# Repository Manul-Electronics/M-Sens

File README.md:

# M-Sens
M-Sens is a family of Open Source and Open Hardware sensors.

For now on this family includes the following devices : 
- [ ] **(Work in progress)** Tropic : A headless relative humidity and temperature sensor build around the HTU31D from TE Connectivity 
- [ ] **(Work in progress)** Mother : A Raspberry Pi based gateway with support for a variaty of communication protocols (Ethernet, Wi-Fi, BLE, Zigbee, ...) built to act as home automation server and central point.

*Other devices could join the family in the future but as I work alone it could be in a very long time.*

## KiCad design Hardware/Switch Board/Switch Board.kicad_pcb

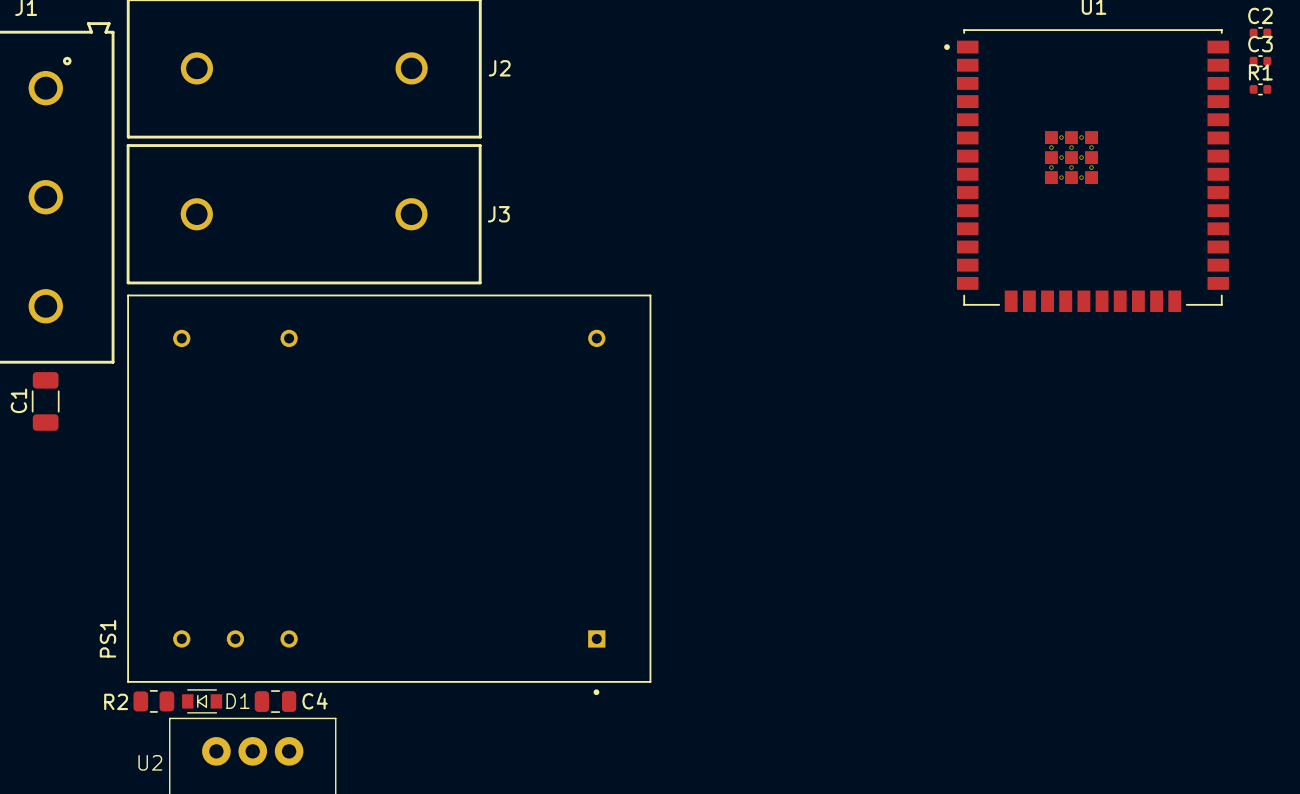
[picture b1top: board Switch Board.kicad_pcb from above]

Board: 2 copper layers, 13 parts (0 on the bottom side), 10 nets, no tracks yet.

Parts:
C1: TBD; C_1206_3216Metric
C2: 1uF; C_0402_1005Metric
C3: 100nF; C_0402_1005Metric
C4: 4.7uF; C_0805_2012Metric
D1: 150224RS73100A; LED_2214
J1: 691218410003
J2, J3: 696106003002
PS1: TMLM_04112; CONV_TMLM_04112
R1: 10K; C_0402_1005Metric
R2: 100R; R_0805_2012Metric
U1: ESP32-WROOM-32UE_(16MB); XCVR_ESP32-WROOM-32UE_(16MB)
U2: 173010335

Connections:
+3V3: C3.1, D1.2 (A), R1.1, U1.2 (3V3), U2.3 (VOUT)
+12V: C4.1, PS1.2 (+VOUT), U2.1 (VIN)
/PSU/L: J1.1, J2.1
/PSU/N: J1.2, J3.1
/mcu/EN: C2.1, R1.2, U1.3 (EN)
Earth_Protective: C1.2, J1.3
GND: C1.1, C2.2, C3.2, C4.2, PS1.3 (-VOUT), R2.2, U1.1 (GND), U1.15 (GND), U1.38 (GND), U1.39_1 (GND), U1.39_2 (GND), U1.39_3 (GND), U1.39_4 (GND), U1.39_5 (GND), U1.39_6 (GND), U1.39_7 (GND), U1.39_8 (GND), U1.39_9 (GND), U2.2 (GND)
unnamed: D1.1 (K), R2.1
unnamed: J2.2, PS1.5 (AC(L))
unnamed: J3.2, PS1.6 (AC(N))

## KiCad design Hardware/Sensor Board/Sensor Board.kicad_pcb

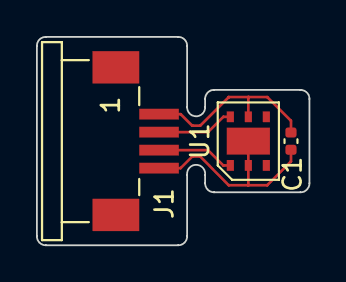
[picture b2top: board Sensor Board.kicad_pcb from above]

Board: 2 copper layers, 15.1 x 11.6 mm, 3 parts (0 on the bottom side), 4 nets.

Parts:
C1: 100nF; C_0402_1005Metric
J1: 68610414422
U1: HTU21DF

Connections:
+3V3: C1.1, J1.1, U1.5 (VDD)
GND: C1.2, J1.4, U1.2 (GND), U1.7 (PAD)
unnamed: J1.2, U1.6 (SCL)
unnamed: J1.3, U1.1 (SDA)

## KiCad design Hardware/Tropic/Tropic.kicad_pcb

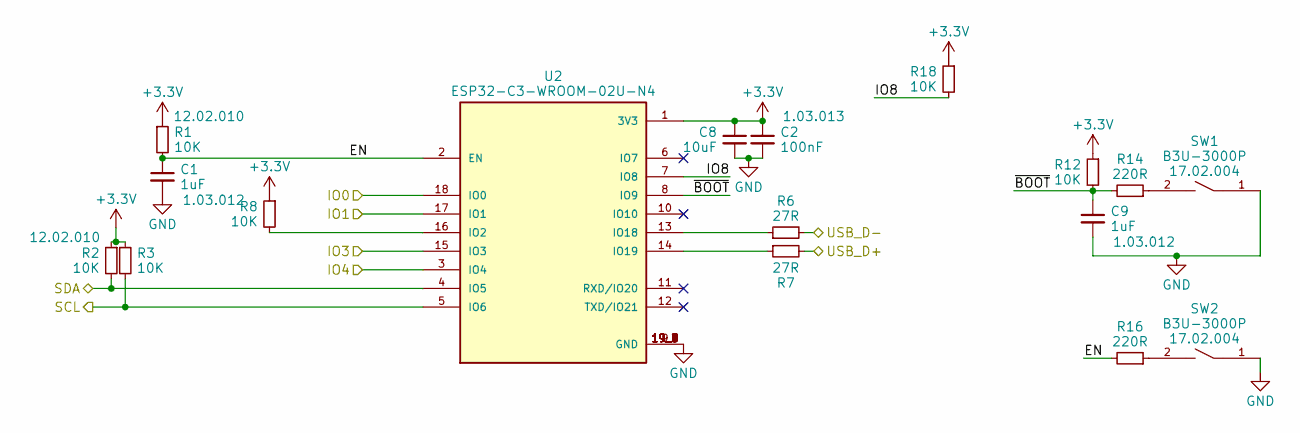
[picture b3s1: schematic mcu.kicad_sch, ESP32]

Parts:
C1, C9: 1uF; C_0402_1005Metric
C2: 100nF; C_0402_1005Metric
C8: 10uF; C_0402_1005Metric
R1, R2, R3, R8, R12, R18: 10K; R_0402_1005Metric
R6, R7: 27R; R_0402_1005Metric
R14, R16: 220R; R_0402_1005Metric
SW1, SW2: B3U-3000P; SW_B3U-3000P; mpn B3U-3000P
U2: ESP32-C3-WROOM-02U-N4; XCVR_ESP32-C3-WROOM-02U-N4

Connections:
+3.3V: C2.1, C8.1, R1.1, R2.1, R3.1, R8.1, R12.1, R18.1, U2.1 (3V3); also elsewhere on the board
/MCU/EN: C1.1, R1.2, R16.2, U2.2 (EN)
/MCU/IO0: U2.18 (IO0); also elsewhere on the board
/MCU/IO1: U2.17 (IO1); also elsewhere on the board
/MCU/IO3: U2.15 (IO3); also elsewhere on the board
/MCU/IO4: U2.3 (IO4); also elsewhere on the board
/MCU/IO8: R18.2, U2.7 (IO8)
/MCU/SCL: R3.2, U2.5 (IO6); also elsewhere on the board
/MCU/SDA: R2.2, U2.4 (IO5); also elsewhere on the board
/MCU/USB_D+: R7.2; also elsewhere on the board
/MCU/USB_D-: R6.2; also elsewhere on the board
/MCU/~BOOT: C9.1, R12.2, R14.2, U2.8 (IO9)
GND: C1.2, C2.2, C8.2, C9.2, SW1.1, SW2.1, U2.9 (GND), U2.19_1 (GND), U2.19_2 (GND), U2.19_3 (GND), U2.19_4 (GND), U2.19_5 (GND), U2.19_6 (GND), U2.19_7 (GND), U2.19_8 (GND), U2.19_9 (GND); also elsewhere on the board
unnamed: R14.1, SW1.2
unnamed: R16.1, SW2.2
unnamed: R8.2, U2.16 (IO2)
unnamed: R6.1, U2.13 (IO18)
unnamed: R7.1, U2.14 (IO19)

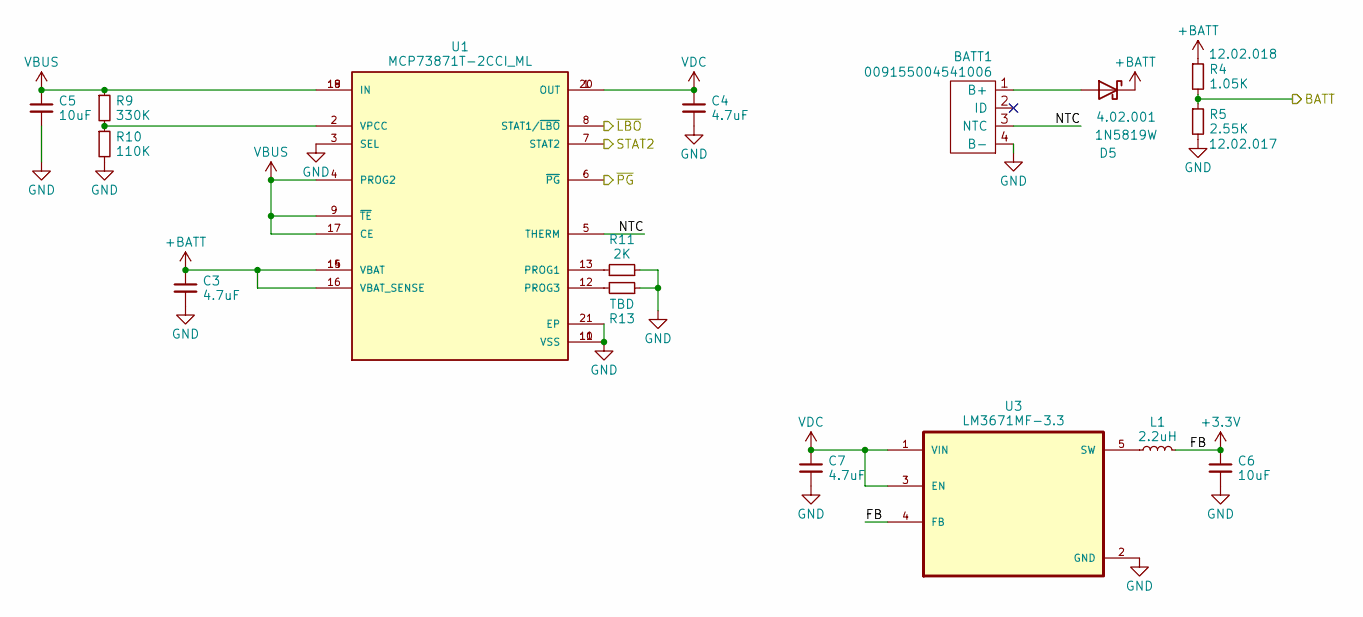
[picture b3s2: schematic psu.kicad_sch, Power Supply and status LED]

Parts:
BATT1: 009155004541006
C3, C4: 4.7uF; C_0603_1608Metric
C5: 10uF; C_0603_1608Metric
C6: 10uF; C_0603_1608Metric; MPN C1608X5R0J106K
C7: 4.7uF; C_0603_1608Metric; MPN C1608X5R0J475K
D5: 1N5819W; D_SOD-123; MPN 1N5819HW-7-F
L1: 2.2uH; CDRH2D14NP-2R2NC
R4: 1.05K; R_0402_1005Metric
R5: 2.55K; R_0402_1005Metric
R9: 330K; R_0402_1005Metric
R10: 110K; R_0402_1005Metric
R11: 2K; R_0402_1005Metric
R13: TBD; R_0402_1005Metric
U1: MCP73871T-2CCI_ML; QFN50P400X400X100-21N
U3: LM3671MF-3.3; SOT-23-5

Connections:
+3.3V: C6.1, L1.2, U3.4 (FB); also elsewhere on the board
+BATT: C3.1, D5.1 (K), R4.1, U1.14 (VBAT), U1.15 (VBAT), U1.16 (VBAT_SENSE)
/MCU/IO0: R4.2, R5.1; also elsewhere on the board
/MCU/IO1: U1.8 (STAT1/~LBO); also elsewhere on the board
/MCU/IO3: U1.6 (~PG); also elsewhere on the board
/MCU/IO4: U1.7 (STAT2); also elsewhere on the board
/Power Supply/NTC: BATT1.3 (NTC), U1.5 (THERM)
GND: BATT1.4 (B-), C3.2, C4.2, C5.2, C6.2, C7.2, R5.2, R10.2, R11.2, R13.2, U1.3 (SEL), U1.10 (VSS), U1.11 (VSS), U1.21 (EP), U3.2 (GND); also elsewhere on the board
unnamed: BATT1.1 (B+), D5.2 (A)
unnamed: R11.1, U1.13 (PROG1)
unnamed: R13.1, U1.12 (PROG3)
unnamed: R9.2, R10.1, U1.2 (VPCC)
unnamed: L1.1, U3.5 (SW)
VBUS: C5.1, R9.1, U1.4 (PROG2), U1.9 (~TE), U1.17 (CE), U1.18 (IN), U1.19 (IN); also elsewhere on the board
VDC: C4.1, C7.1, U1.1 (OUT), U1.20 (OUT), U3.1 (VIN), U3.3 (EN)

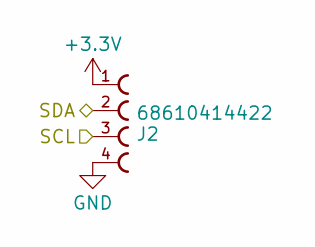
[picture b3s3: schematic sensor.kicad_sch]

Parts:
J2: 68610414422; MPN 68610414422

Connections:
+3.3V: J2.1; also elsewhere on the board
/MCU/SCL: J2.3; also elsewhere on the board
/MCU/SDA: J2.2; also elsewhere on the board
GND: J2.4; also elsewhere on the board

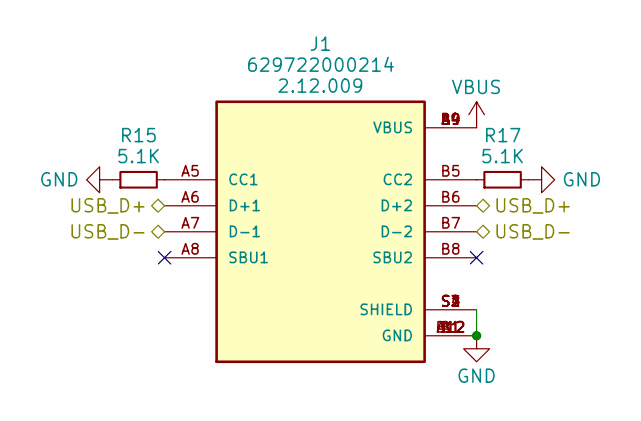
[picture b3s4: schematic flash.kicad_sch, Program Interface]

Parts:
J1: 629722000214; PARTREV 001.001
R15, R17: 5.1K; R_0402_1005Metric

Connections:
/MCU/USB_D+: J1.A6 (D+1), J1.B6 (D+2); also elsewhere on the board
/MCU/USB_D-: J1.A7 (D-1), J1.B7 (D-2); also elsewhere on the board
GND: J1.A1 (GND), J1.A12 (GND), J1.B1 (GND), J1.B12 (GND), J1.S1 (SHIELD), J1.S2 (SHIELD), J1.S3 (SHIELD), J1.S4 (SHIELD), R15.1, R17.2; also elsewhere on the board
unnamed: J1.A5 (CC1), R15.2
unnamed: J1.B5 (CC2), R17.1
VBUS: J1.A4 (VBUS), J1.A9 (VBUS), J1.B4 (VBUS), J1.B9 (VBUS); also elsewhere on the board

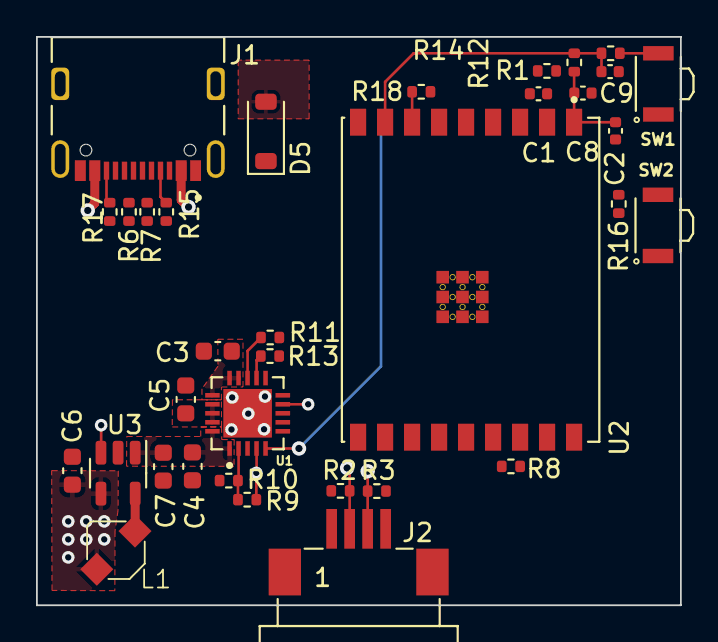
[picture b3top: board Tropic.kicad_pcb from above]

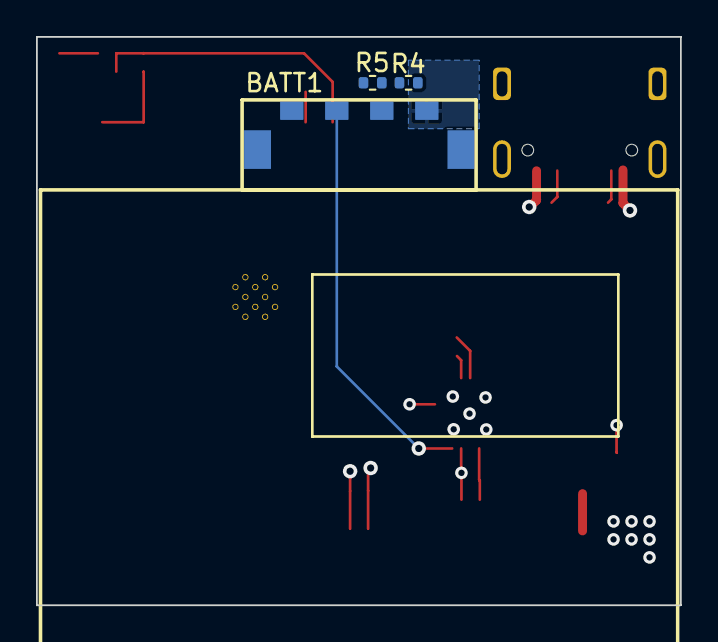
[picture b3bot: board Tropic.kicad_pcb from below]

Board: 4 copper layers, 35.8 x 31.6 mm, 37 parts (3 on the bottom side), 29 nets.

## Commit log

2024-01-31 Added Tropic and Tropic Thunder PCBs
2024-01-31 Removed doubled Pi Matching and add LED for voltage monitoring
2024-02-01 Completed design V1
2024-02-01 Add spacing around rf line
2024-02-02 Latest changes
2024-02-26 Rework on components
2024-12-13 Clear Hardware folder, reamking from scratch
2024-12-14 New Sensor PCB design
2024-12-19 Created Switch Board PCB Project
2024-12-31 Completed Power Supply scheamatic + started to place components
